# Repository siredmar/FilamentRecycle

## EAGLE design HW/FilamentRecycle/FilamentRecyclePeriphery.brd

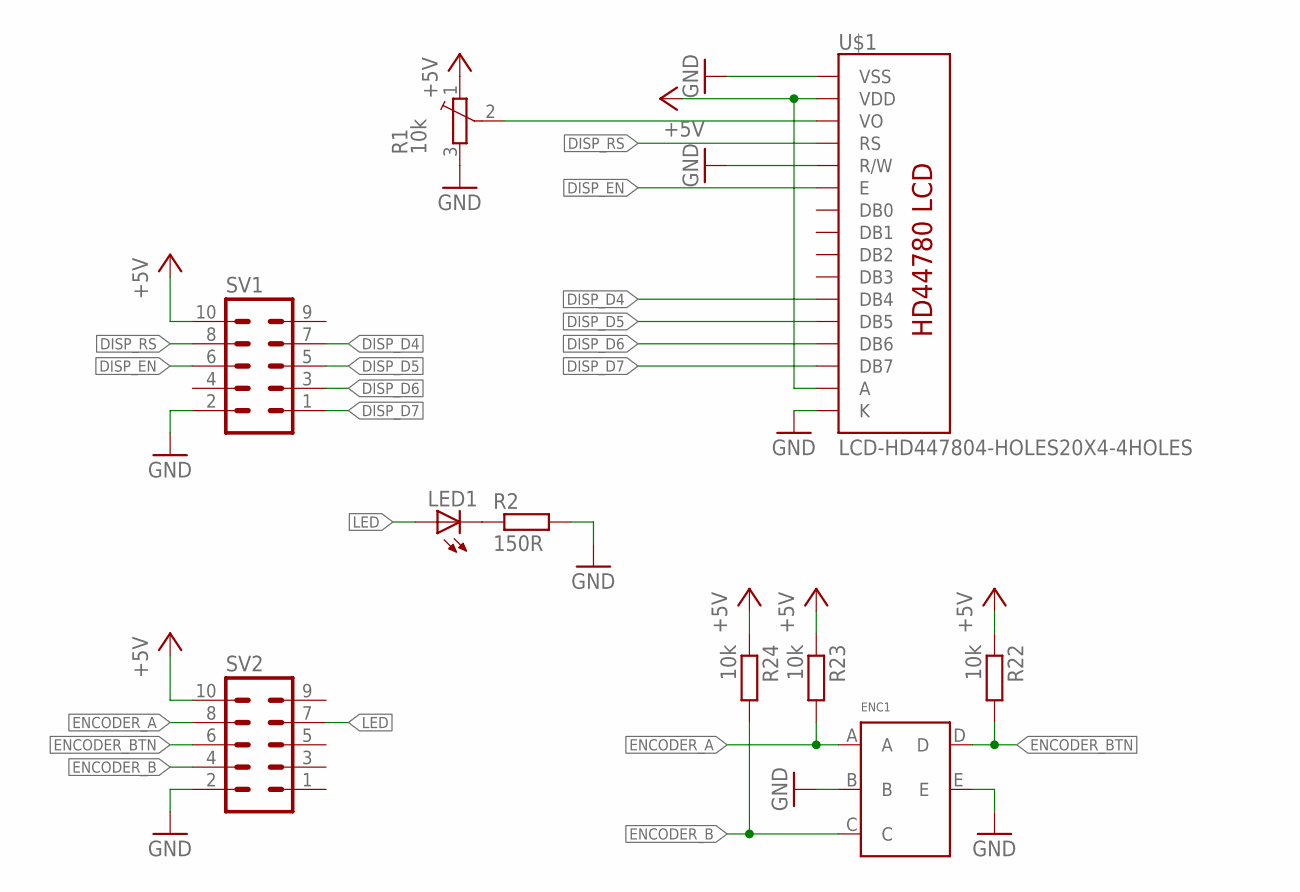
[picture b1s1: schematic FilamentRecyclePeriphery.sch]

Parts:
ENC1: ENCODER
LED1: LED3MM
R1: 10k; 35WR5KLFTR
R2: 150R; R0603
R22, R23, R24: 10k; R0603
SV1, SV2: ML10
U$1: LCD-HD447804-HOLES20X4-4HOLES; LCD-20X4-4HOLES

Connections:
+5V: R1.1 (E), R22.1, R23.1, R24.1, SV1.10, SV2.10, U$1.P$2 (VDD), U$1.P$15 (A)
DISP_D4: SV1.7, U$1.P$11 (DB4)
DISP_D5: SV1.5, U$1.P$12 (DB5)
DISP_D6: SV1.3, U$1.P$13 (DB6)
DISP_D7: SV1.1, U$1.P$14 (DB7)
DISP_EN: SV1.6, U$1.P$6 (E)
DISP_RS: SV1.8, U$1.P$4 (RS)
ENCODER_A: ENC1.A, R23.2, SV2.8
ENCODER_B: ENC1.C, R24.2, SV2.4
ENCODER_BTN: ENC1.D, R22.2, SV2.6
GND: ENC1.B, ENC1.E, R1.3 (A), R2.2, SV1.2, SV2.2, U$1.P$1 (VSS), U$1.P$5 (R/W), U$1.P$16 (K)
LED: LED1.A, SV2.7
unnamed: LED1.K (C), R2.1
unnamed: R1.2 (S), U$1.P$3 (VO)

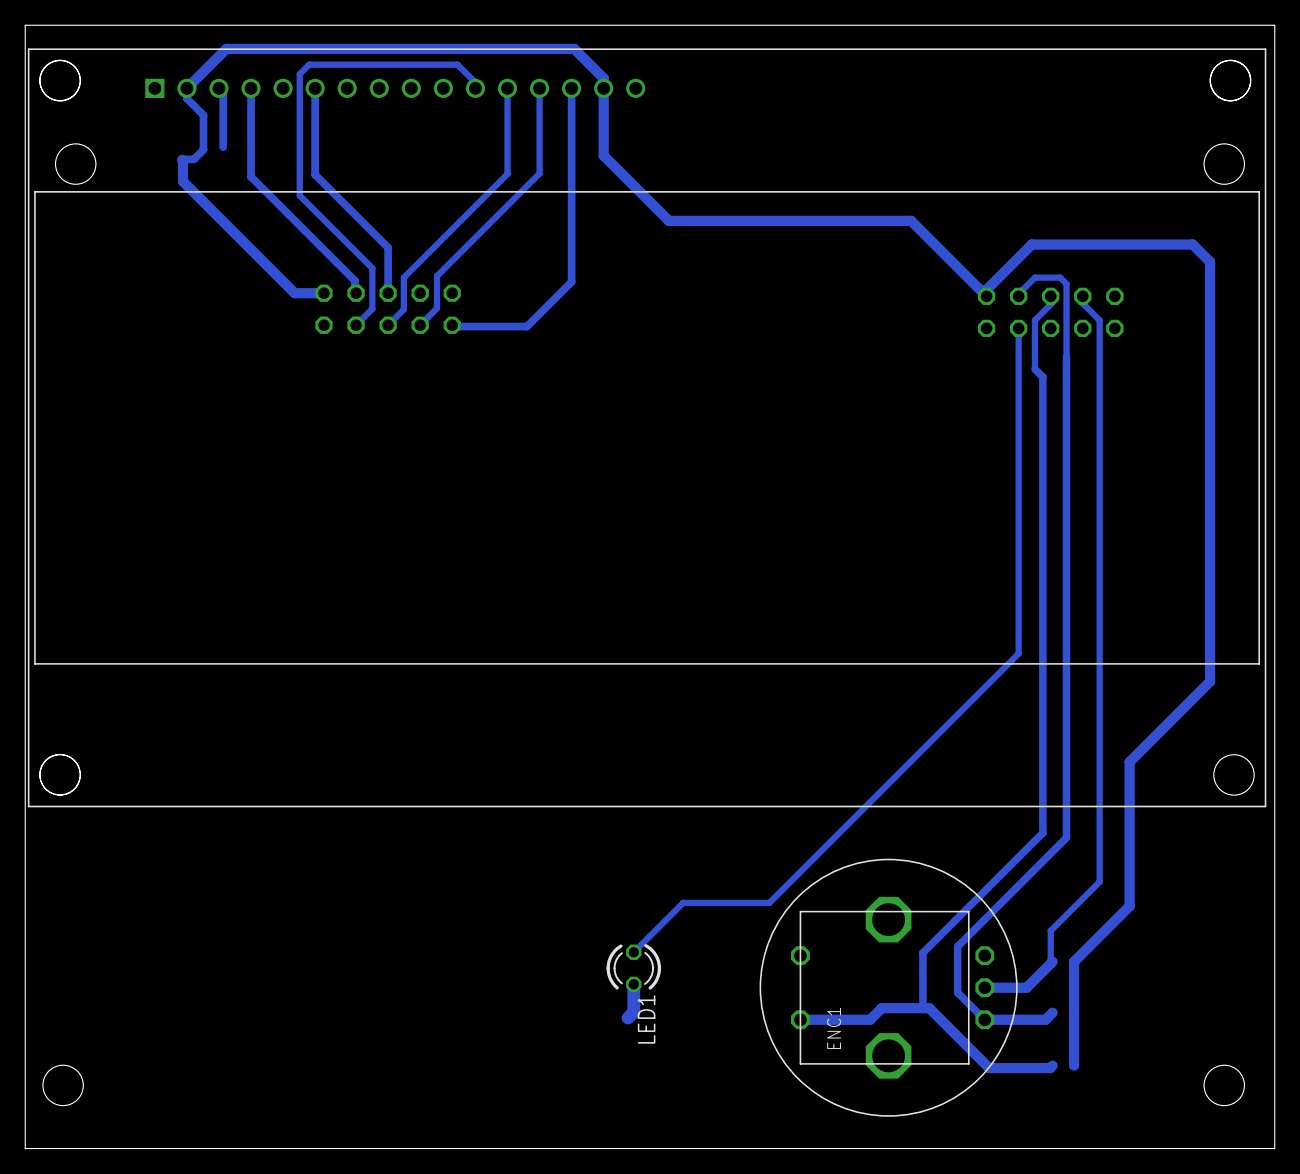
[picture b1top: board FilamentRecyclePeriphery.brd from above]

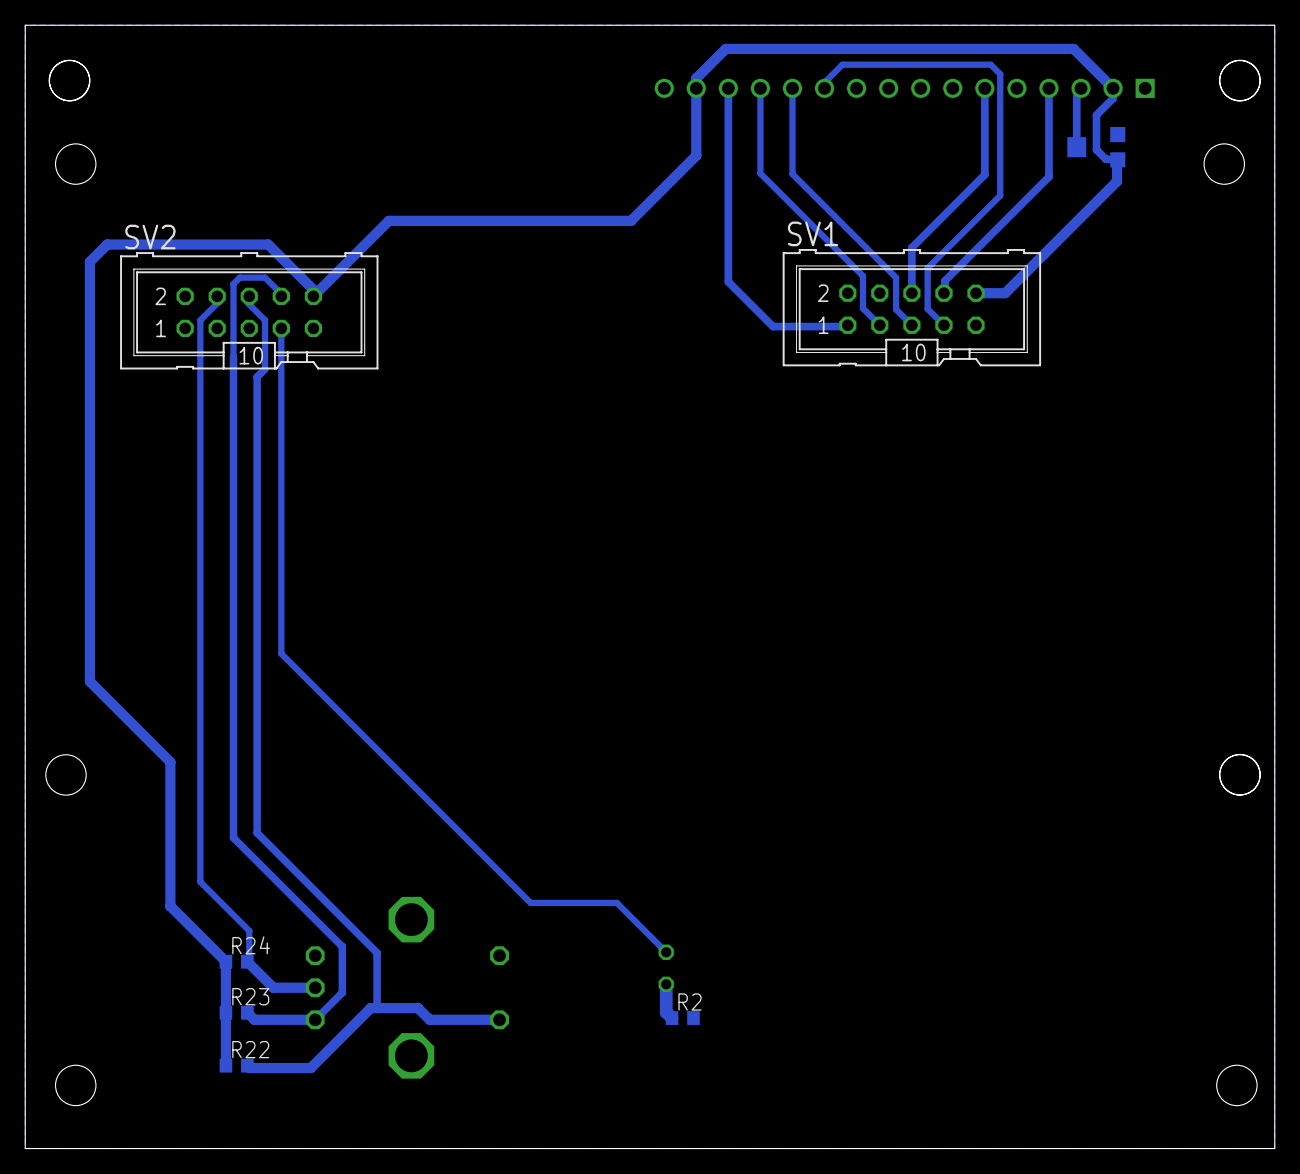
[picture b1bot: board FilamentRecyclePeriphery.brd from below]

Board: 2 copper layers, 99.0 x 89.0 mm, 10 parts (7 on the bottom side), 14 nets.

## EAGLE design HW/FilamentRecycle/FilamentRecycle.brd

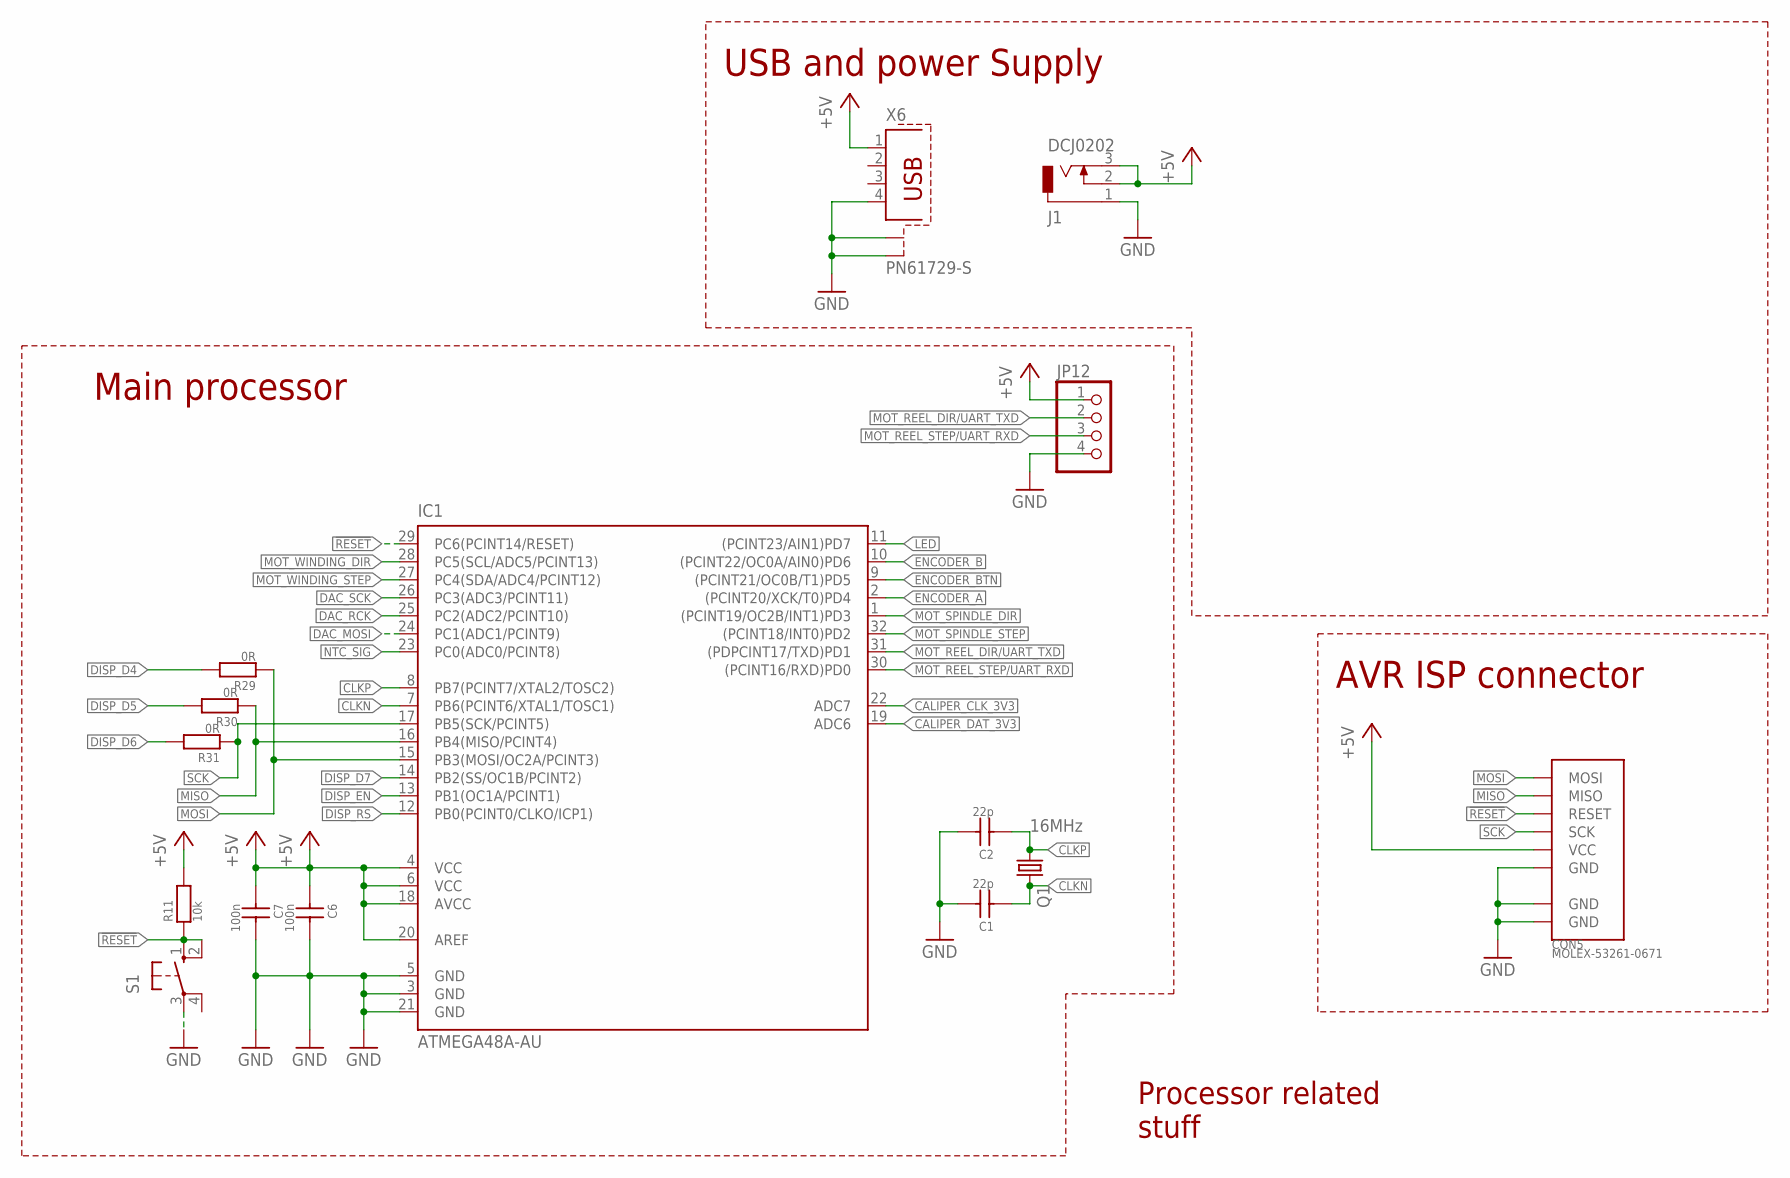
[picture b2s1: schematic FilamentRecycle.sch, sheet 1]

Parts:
C1, C2: 22p; C0603
C6, C7: 100n; C0603
CON5: MOLEX-53261-0671
IC1: ATMEGA48A-AU; TQFP32
J1: DCJ0202
JP12: PINHD-1X4; 1X04
Q1: 16MHz; HC49UP
R11: 10k; R0603
R29, R30, R31: 0R; R0603
S1: 10-XX; B3F-10XX
X6: PN61729-S

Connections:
!RESET: CON5.3 (RESET), IC1.29 (PC6(PCINT14/RESET)), R11.1, S1.1 (S), S1.2 (S1)
+5V: C6.1, C7.1, CON5.5 (VCC), IC1.4 (VCC), IC1.6 (VCC), IC1.18 (AVCC), IC1.20 (AREF), J1.2, J1.3, JP12.1, R11.2, X6.1; also elsewhere on the board
CALIPER_CLK_3V3: IC1.22 (ADC7); also elsewhere on the board
CALIPER_DAT_3V3: IC1.19 (ADC6); also elsewhere on the board
CLKN: C1.1, IC1.7 (PB6(PCINT6/XTAL1/TOSC1)), Q1.2
CLKP: C2.1, IC1.8 (PB7(PCINT7/XTAL2/TOSC2)), Q1.1
DAC_MOSI: IC1.24 (PC1(ADC1/PCINT9)); also elsewhere on the board
DAC_RCK: IC1.25 (PC2(ADC2/PCINT10)); also elsewhere on the board
DAC_SCK: IC1.26 (PC3(ADC3/PCINT11)); also elsewhere on the board
DISP_D4: R29.2; also elsewhere on the board
DISP_D5: R30.2; also elsewhere on the board
DISP_D6: R31.2; also elsewhere on the board
DISP_D7: IC1.14 (PB2(SS/OC1B/PCINT2)); also elsewhere on the board
DISP_EN: IC1.13 (PB1(OC1A/PCINT1)); also elsewhere on the board
DISP_RS: IC1.12 (PB0(PCINT0/CLKO/ICP1)); also elsewhere on the board
ENCODER_A: IC1.2 ((PCINT20/XCK/T0)PD4); also elsewhere on the board
ENCODER_B: IC1.10 ((PCINT22/OC0A/AIN0)PD6); also elsewhere on the board
ENCODER_BTN: IC1.9 ((PCINT21/OC0B/T1)PD5); also elsewhere on the board
GND: C1.2, C2.2, C6.2, C7.2, CON5.6 (GND), CON5.GND@1 (GND), CON5.GND@2 (GND), IC1.3 (GND), IC1.5 (GND), IC1.21 (GND), J1.1, JP12.4, S1.3, X6.4, X6.S1, X6.S2; also elsewhere on the board
LED: IC1.11 ((PCINT23/AIN1)PD7); also elsewhere on the board
MISO: CON5.2 (MISO), IC1.16 (PB4(MISO/PCINT4)), R30.1
MOSI: CON5.1 (MOSI), IC1.15 (PB3(MOSI/OC2A/PCINT3)), R29.1
MOT_REEL_DIR/UART_TXD: IC1.31 ((PDPCINT17/TXD)PD1), JP12.2; also elsewhere on the board
MOT_REEL_STEP/UART_RXD: IC1.30 ((PCINT16/RXD)PD0), JP12.3; also elsewhere on the board
MOT_SPINDLE_DIR: IC1.1 ((PCINT19/OC2B/INT1)PD3); also elsewhere on the board
MOT_SPINDLE_STEP: IC1.32 ((PCINT18/INT0)PD2); also elsewhere on the board
MOT_WINDING_DIR: IC1.28 (PC5(SCL/ADC5/PCINT13)); also elsewhere on the board
MOT_WINDING_STEP: IC1.27 (PC4(SDA/ADC4/PCINT12)); also elsewhere on the board
NTC_SIG: IC1.23 (PC0(ADC0/PCINT8)); also elsewhere on the board
SCK: CON5.4 (SCK), IC1.17 (PB5(SCK/PCINT5)), R31.1

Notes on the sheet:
Main processor
AVR ISP connector
USB and power Supply
Processor related stuff

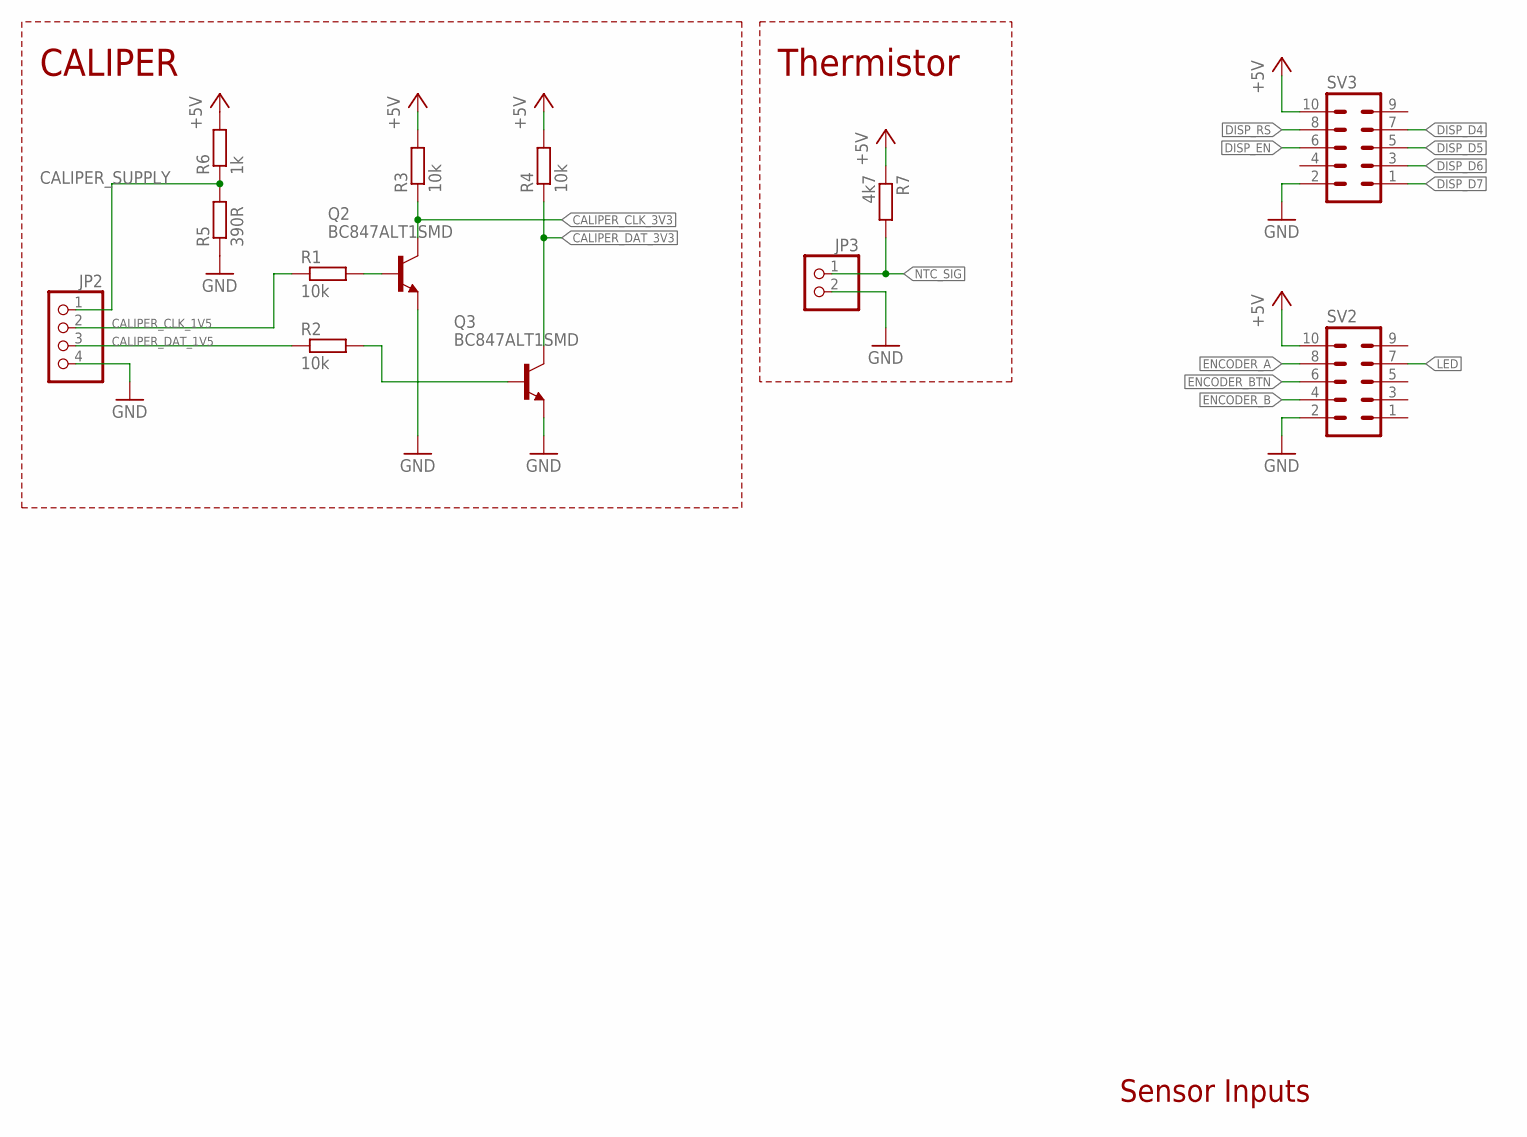
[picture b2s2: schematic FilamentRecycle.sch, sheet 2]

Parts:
JP2: PINHD-1X4; 1X04
JP3: PINHD-1X2; 1X02
Q2, Q3: BC847ALT1SMD; SOT23
R1, R2, R3, R4: 10k; R0603
R5: 390R; R0603
R6: 1k; R0603
R7: 4k7; R0603
SV2, SV3: ML10

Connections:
+5V: R3.2, R4.2, R6.2, R7.1, SV2.10, SV3.10; also elsewhere on the board
CALIPER_CLK_1V5: JP2.2, R1.1
CALIPER_CLK_3V3: Q2.3 (C), R3.1; also elsewhere on the board
CALIPER_DAT_1V5: JP2.3, R2.1
CALIPER_DAT_3V3: Q3.3 (C), R4.1; also elsewhere on the board
CALIPER_SUPPLY: JP2.1, R5.2, R6.1
DISP_D4: SV3.7; also elsewhere on the board
DISP_D5: SV3.5; also elsewhere on the board
DISP_D6: SV3.3; also elsewhere on the board
DISP_D7: SV3.1; also elsewhere on the board
DISP_EN: SV3.6; also elsewhere on the board
DISP_RS: SV3.8; also elsewhere on the board
ENCODER_A: SV2.8; also elsewhere on the board
ENCODER_B: SV2.4; also elsewhere on the board
ENCODER_BTN: SV2.6; also elsewhere on the board
GND: JP2.4, JP3.2, Q2.2 (E), Q3.2 (E), R5.1, SV2.2, SV3.2; also elsewhere on the board
LED: SV2.7; also elsewhere on the board
unnamed: Q2.1 (B), R1.2
unnamed: Q3.1 (B), R2.2
NTC_SIG: JP3.1, R7.2; also elsewhere on the board

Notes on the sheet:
CALIPER
Thermistor
Sensor Inputs

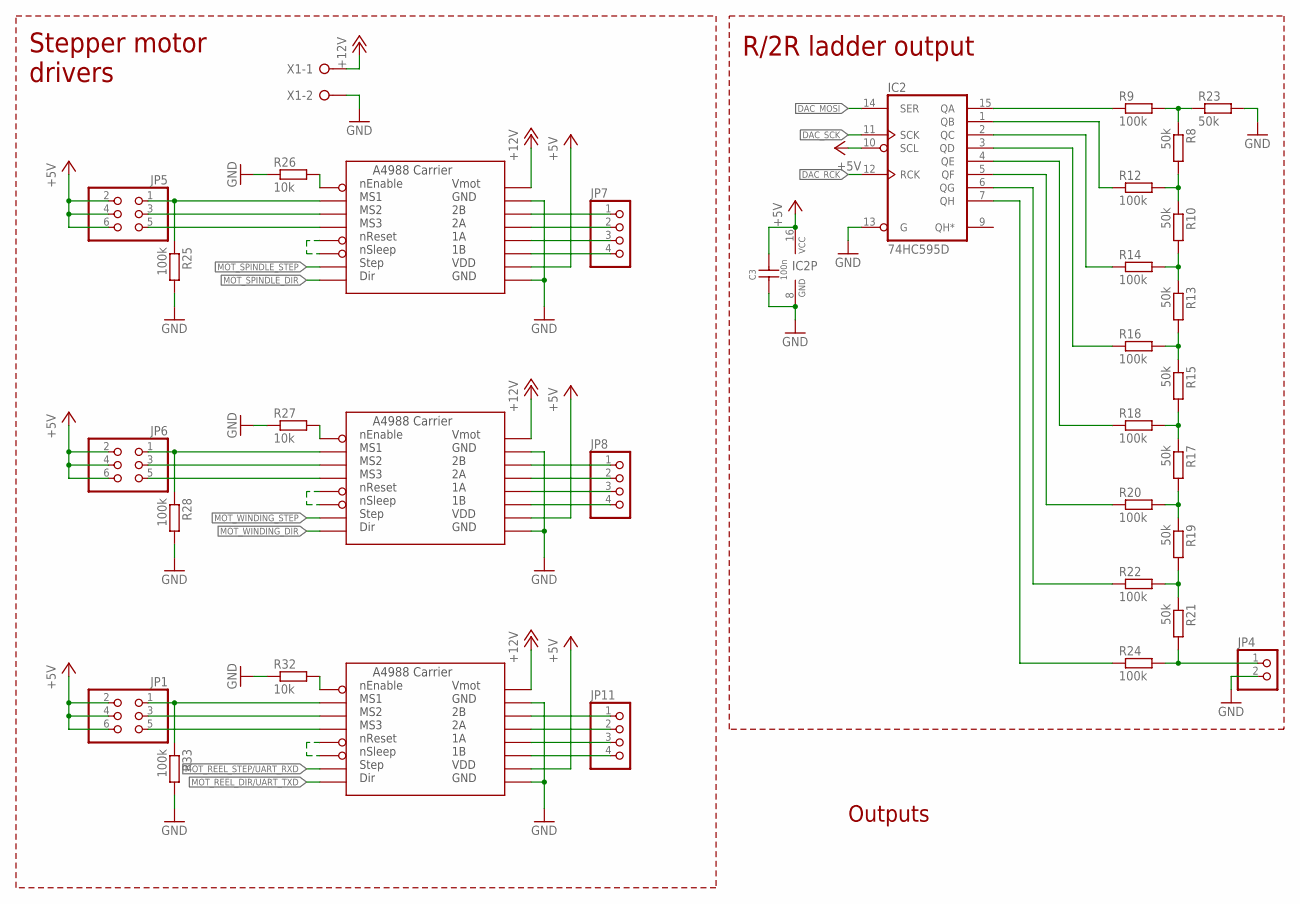
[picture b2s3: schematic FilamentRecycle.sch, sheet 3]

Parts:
C3: 100n; C0603
IC2: 74HC595D; SO16
JP1, JP5, JP6: PINHD-2X3; 2X03
JP4: PINHD-1X2; 1X02
JP7, JP8, JP11: PINHD-1X4; 1X04
R8, R10, R13, R15, R17, R19, R21, R23: 50k; R0603
R9, R12, R14, R16, R18, R20, R22, R24, R25, R28, R33: 100k; R0603
R26, R27, R32: 10k; R0603
U$7, U$9, U$14: A4988BREAKOUT
X1: W237-02P; W237-132

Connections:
!MOT_SPINDLE_EN: R26.2, U$7.EN
!MOT_WINDING_EN: R27.2, U$14.EN
!MOT_WINDING_EN1: R32.2, U$9.EN
+5V: C3.2, IC2.10 (SCL), IC2.16 (VCC), JP1.2, JP1.4, JP1.6, JP5.2, JP5.4, JP5.6, JP6.2, JP6.4, JP6.6, U$7.VDD, U$9.VDD, U$14.VDD; also elsewhere on the board
+12V: U$7.VMOT, U$9.VMOT, U$14.VMOT, X1.1
DAC_MOSI: IC2.14 (SER); also elsewhere on the board
DAC_RCK: IC2.12 (RCK); also elsewhere on the board
DAC_SCK: IC2.11 (SCK); also elsewhere on the board
GND: C3.1, IC2.8 (GND), IC2.13 (G), JP4.2, R23.2, R25.2, R26.1, R27.1, R28.2, R32.1, R33.2, U$7.GND@0 (GND), U$7.GND@1 (GND), U$9.GND@0 (GND), U$9.GND@1 (GND), U$14.GND@0 (GND), U$14.GND@1 (GND), X1.2; also elsewhere on the board
MOT_REEL_DIR/UART_TXD: U$9.DIR; also elsewhere on the board
MOT_REEL_STEP/UART_RXD: U$9.STEP; also elsewhere on the board
MOT_SPINDLE_DIR: U$7.DIR; also elsewhere on the board
MOT_SPINDLE_STEP: U$7.STEP; also elsewhere on the board
MOT_WINDING_DIR: U$14.DIR; also elsewhere on the board
MOT_WINDING_STEP: U$14.STEP; also elsewhere on the board
unnamed: JP1.5, U$9.MS3
unnamed: JP1.1, R33.1, U$9.MS1
unnamed: JP4.1, R21.2, R24.2
unnamed: R19.2, R21.1, R22.2
unnamed: JP1.3, U$9.MS2
unnamed: R17.2, R19.1, R20.2
unnamed: JP11.1, U$9.2B
unnamed: R15.2, R17.1, R18.2
unnamed: R13.2, R15.1, R16.2
unnamed: R10.2, R13.1, R14.2
unnamed: R8.2, R10.1, R12.2
unnamed: R8.1, R9.2, R23.1
unnamed: IC2.15 (QA), R9.1
unnamed: IC2.1 (QB), R12.1
unnamed: IC2.2 (QC), R14.1
unnamed: IC2.3 (QD), R16.1
unnamed: IC2.4 (QE), R18.1
unnamed: IC2.5 (QF), R20.1
unnamed: IC2.6 (QG), R22.1
unnamed: IC2.7 (QH), R24.1
unnamed: JP5.5, U$7.MS3
unnamed: U$7.RST, U$7.SLP (SLEEP)
unnamed: JP5.1, R25.1, U$7.MS1
unnamed: JP5.3, U$7.MS2
unnamed: JP7.1, U$7.2B
unnamed: JP7.2, U$7.2A
unnamed: JP7.3, U$7.1A
unnamed: JP7.4, U$7.1B
unnamed: JP11.2, U$9.2A
unnamed: JP6.5, U$14.MS3
unnamed: JP6.1, R28.1, U$14.MS1
unnamed: JP6.3, U$14.MS2
unnamed: JP8.1, U$14.2B
unnamed: JP8.2, U$14.2A
unnamed: JP8.3, U$14.1A
unnamed: JP8.4, U$14.1B
unnamed: U$14.RST, U$14.SLP (SLEEP)
unnamed: JP11.3, U$9.1A
unnamed: JP11.4, U$9.1B
unnamed: U$9.RST, U$9.SLP (SLEEP)

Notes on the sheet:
R/2R ladder output
Stepper motor drivers
Outputs

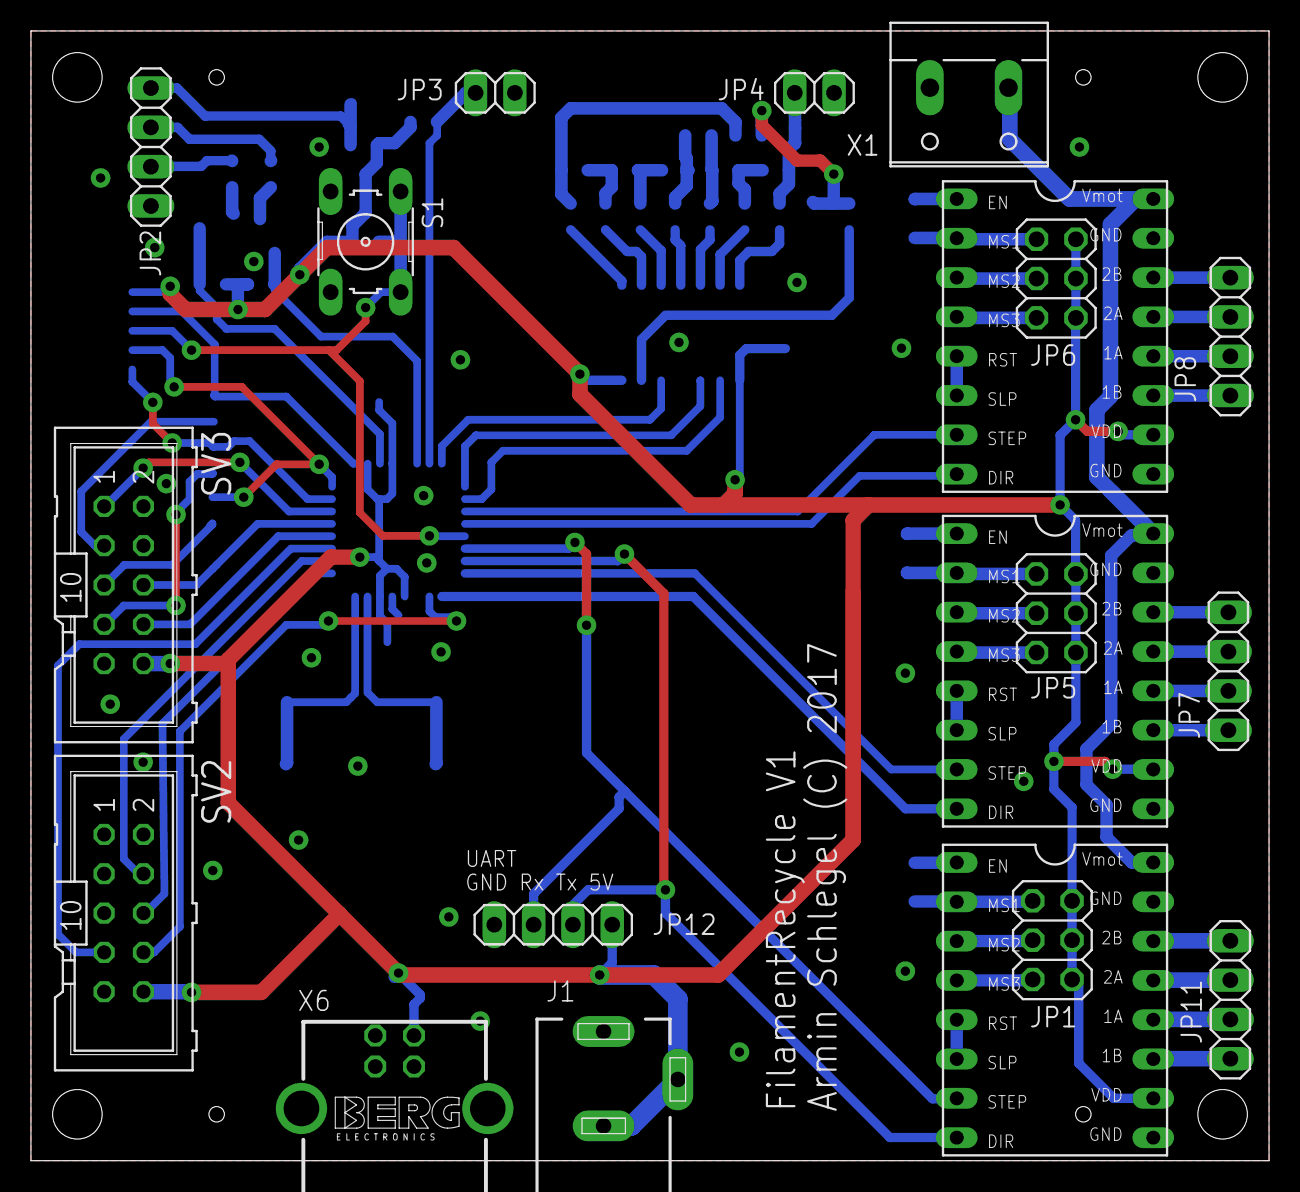
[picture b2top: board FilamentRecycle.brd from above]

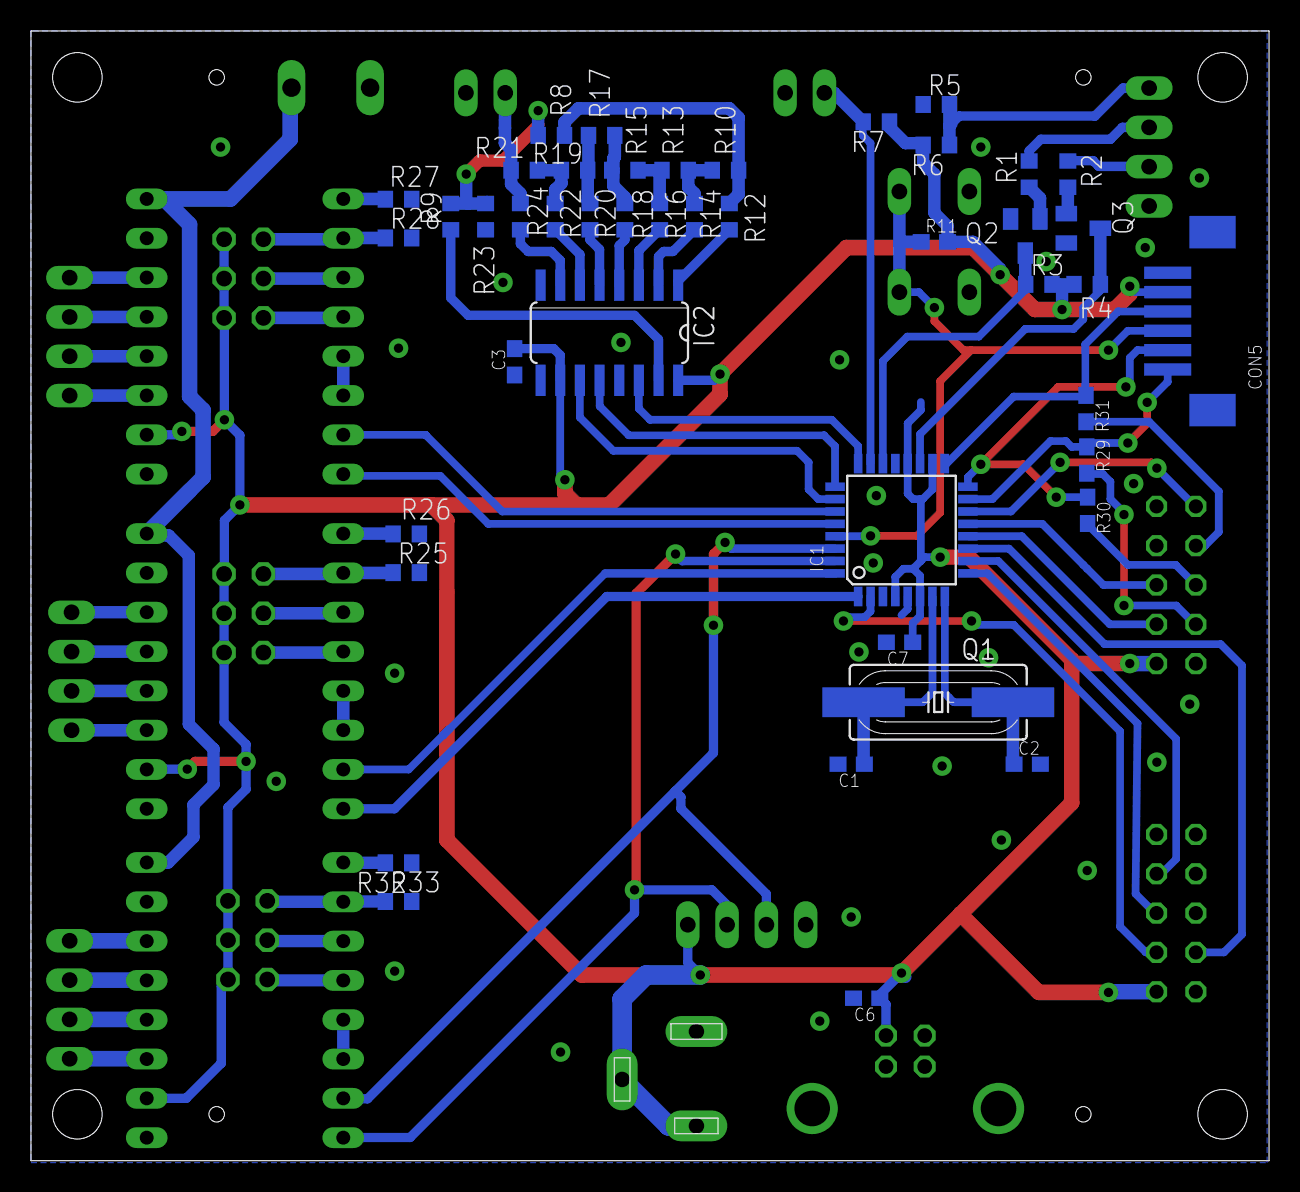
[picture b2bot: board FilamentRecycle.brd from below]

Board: 2 copper layers, 80.0 x 73.0 mm, 63 parts (44 on the bottom side), 79 nets.

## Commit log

2017-01-15 Initial commit - added caliper mechanic stl files
2017-01-15 Added reference source for reading the caliper with arduino nano
2017-01-15 Added Hw - still in work
2017-01-17 Reading the caliper via uart working
2017-01-17 Deletec obsolete files
2017-01-17 Moved files
2017-01-17 first version of NTC handling
2017-01-20 Temperatur reading working with NTC3950 thermistor
2017-01-20 Nicify serial output
2017-01-21 Schematic and board work
2017-01-22 R2R ladder output working via HC595 shift register
2017-01-23 Eagle brd RC1
2017-06-19 First tests of target hardware. DAC, Caliper and thermistor working
2017-06-21 Added LCD library, Fixed hw bug (series resistors for LCD removed)
2017-06-21 Added rotary encoder and application menu
2017-06-21 Added Periphery board
2017-06-21 Added LED Handling

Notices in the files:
HW/FilamentRecycle/FilamentRecycle.brd:
Armin Schlegel (C) 2017
